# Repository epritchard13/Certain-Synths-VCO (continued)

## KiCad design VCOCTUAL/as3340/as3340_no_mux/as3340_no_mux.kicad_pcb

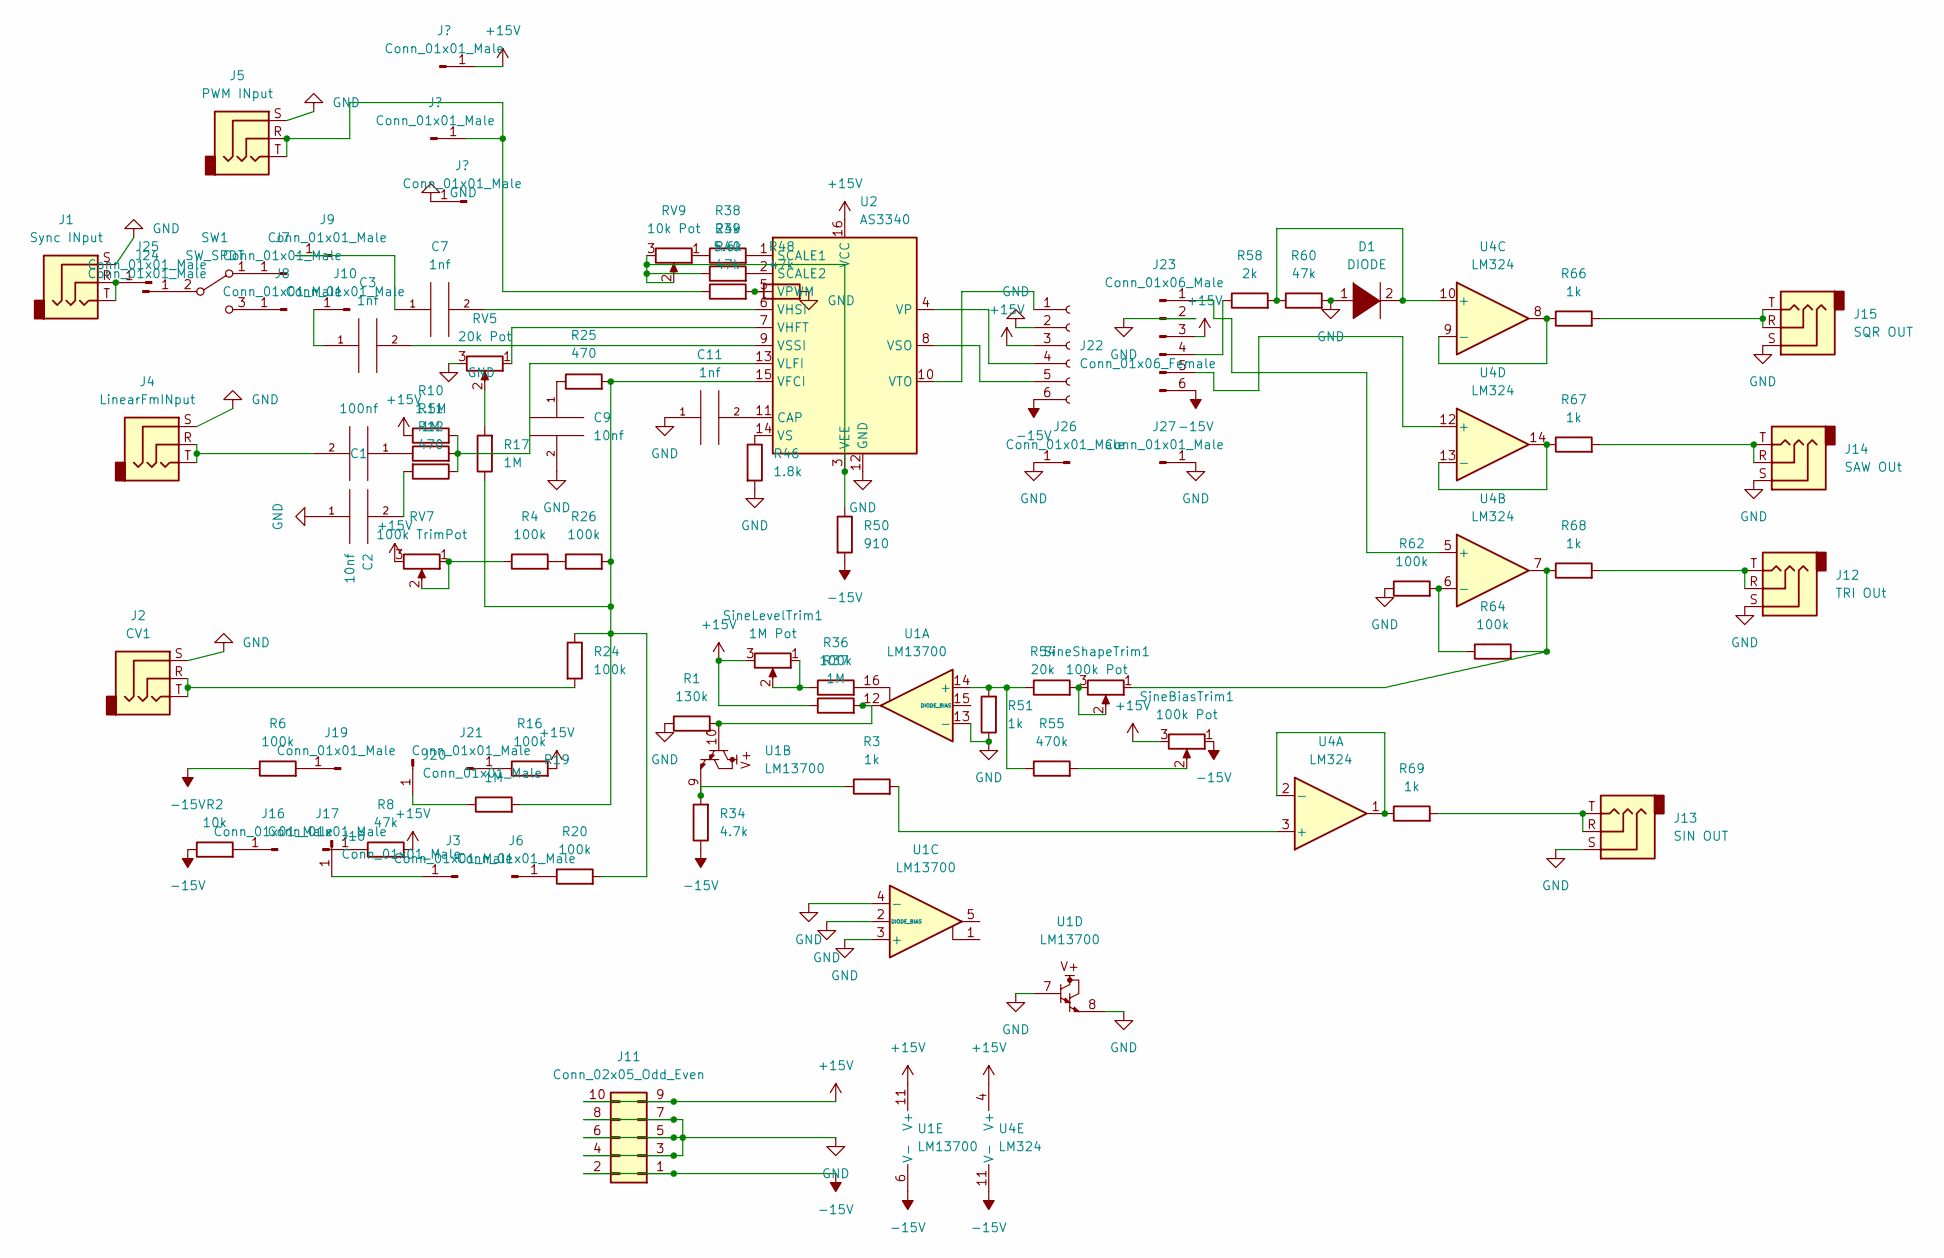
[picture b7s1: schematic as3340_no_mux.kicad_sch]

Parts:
C1: 100nf; C_Disc_D3.0mm_W1.6mm_P2.50mm
C2, C9: 10nf; C_1206_3216Metric_Pad1.33x1.80mm_HandSolder
C3, C7, C11: 1nf; C_1206_3216Metric_Pad1.33x1.80mm_HandSolder
D1: DIODE; C_Disc_D3.0mm_W1.6mm_P2.50mm
J1: Sync INput; Jack_3.5mm_Switronic_ST-005-G_horizontal
J2: CV1; Jack_3.5mm_Switronic_ST-005-G_horizontal
J3, J6, J7, J8, J9, J10, J16, J17, J18, J19, J20, J21, J24, J25, J26, J27: Conn_01x01_Male; PinHeader_1x01_P2.54mm_Vertical
J4: LinearFmINput; Jack_3.5mm_Switronic_ST-005-G_horizontal
J5: PWM INput; Jack_3.5mm_Switronic_ST-005-G_horizontal
J11: Conn_02x05_Odd_Even; PinHeader_2x05_P2.54mm_Vertical
J12: TRI OUt; Jack_3.5mm_Switronic_ST-005-G_horizontal
J13: SIN OUT; Jack_3.5mm_Switronic_ST-005-G_horizontal
J14: SAW OUt; Jack_3.5mm_Switronic_ST-005-G_horizontal
J15: SQR OUT; Jack_3.5mm_Switronic_ST-005-G_horizontal
J22: Conn_01x06_Female; PinHeader_1x06_P2.54mm_Vertical
J23: Conn_01x06_Male; PinHeader_1x06_P2.54mm_Vertical
R1: 130k; R_1206_3216Metric_Pad1.30x1.75mm_HandSolder
R2: 10k; R_1206_3216Metric_Pad1.30x1.75mm_HandSolder
R3, R51, R66, R67, R68, R69: 1k; R_1206_3216Metric_Pad1.30x1.75mm_HandSolder
R4, R6, R16, R20, R24, R26, R36, R62, R64: 100k; R_1206_3216Metric_Pad1.30x1.75mm_HandSolder
R8, R40, R48, R60: 47k; R_Axial_DIN0204_L3.6mm_D1.6mm_P5.08mm_Horizontal
R10: 1.5M; R_Axial_DIN0204_L3.6mm_D1.6mm_P5.08mm_Horizontal
R11, R17, R19, R37: 1M; R_Axial_DIN0204_L3.6mm_D1.6mm_P5.08mm_Horizontal
R12, R25: 470; R_1206_3216Metric_Pad1.30x1.75mm_HandSolder
R34: 4.7k; R_1206_3216Metric_Pad1.30x1.75mm_HandSolder
R38: 24k; R_1206_3216Metric_Pad1.30x1.75mm_HandSolder
R39: 5.6k; R_Axial_DIN0204_L3.6mm_D1.6mm_P5.08mm_Horizontal
R46: 1.8k; R_1206_3216Metric_Pad1.30x1.75mm_HandSolder
R50: 910; R_1206_3216Metric_Pad1.30x1.75mm_HandSolder
R54: 20k; R_1206_3216Metric_Pad1.30x1.75mm_HandSolder
R55: 470k; R_1206_3216Metric_Pad1.30x1.75mm_HandSolder
R58: 2k; R_1206_3216Metric_Pad1.30x1.75mm_HandSolder
RV5: 20k Pot; Potentiometer_ACP_CA6-H2,5_Horizontal
RV7: 100k TrimPot; Potentiometer_ACP_CA6-H2,5_Horizontal
RV9: 10k Pot; Potentiometer_ACP_CA6-H2,5_Horizontal
SW1: SW_SPDT; Potentiometer_ACP_CA6-H2,5_Horizontal
SineBiasTrim1: 100k Pot; Potentiometer_ACP_CA6-H2,5_Horizontal
SineLevelTrim1: 1M Pot; Potentiometer_ACP_CA6-H2,5_Horizontal
SineShapeTrim1: 100k Pot; Potentiometer_ACP_CA6-H2,5_Horizontal
U1: LM13700; DIP-16_W7.62mm
U2: AS3340; DIP-16_W7.62mm
U4: LM324; DIP-14_W7.62mm

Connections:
+15V: J11.9, J11.10, J22.3, J23.3, R8.2, R10.1, R16.2, R37.1, RV7.3, SineBiasTrim1.3, SineLevelTrim1.3, U1.11 (V+), U2.16 (VCC), U4.4 (V+)
-15V: J11.1, J11.2, J22.6, J23.6, R2.1, R6.1, R34.1, R50.2, SineBiasTrim1.1, U1.6 (V-), U4.11 (V-)
GND: C2.1, C9.2, C11.1, D1.1 (K), J1.S, J2.S, J4.S, J5.S, J11.3, J11.4, J11.5, J11.6, J11.7, J11.8, J12.S, J13.S, J14.S, J15.S, J22.2, J23.2, J26.1, J27.1, R1.1, R46.2, R48.2, R51.1, R60.2, R62.1, RV5.3, U1.2 (DIODE_BIAS), U1.3 (+), U1.4 (-), U1.7, U1.8, U1.13 (-), U2.12 (GND)
unnamed: C1.1, R11.1
unnamed: C1.2, J4.R, J4.T
unnamed: C2.2, R12.2
unnamed: C3.1, J10.1
unnamed: C3.2, U2.9 (VSSI)
unnamed: C7.1, J9.1
unnamed: C7.2, U2.6 (VHSI)
unnamed: C9.1, R25.1
unnamed: C11.2, U2.11 (CAP)
unnamed: D1.2 (A), R58.2, R60.1, U4.10 (+)
unnamed: J1.R, J1.T, J25.1
unnamed: J3.1, J18.1
unnamed: J7.1, SW1.1 (A)
unnamed: J8.1, SW1.3 (C)
unnamed: J22.1, U2.10 (VTO)
unnamed: J22.4, U2.4 (VP)
unnamed: J22.5, U2.8 (VSO)
unnamed: J24.1, SW1.2 (B)
unnamed: J16.1, R2.2
unnamed: J19.1, R6.2
unnamed: J17.1, R8.1
unnamed: R10.2, R11.2, R12.1, U2.13 (VLFI)
unnamed: J21.1, R16.1
unnamed: R17.1, R19.2, R20.2, R24.1, R25.2, R26.2, U2.15 (VFCI)
unnamed: R17.2, RV5.2
unnamed: J20.1, R19.1
unnamed: J6.1, R20.1
unnamed: J2.R, J2.T, R24.2
unnamed: R4.2, R26.1
unnamed: R3.1, R34.2, U1.9
unnamed: R36.1, SineLevelTrim1.1, SineLevelTrim1.2
unnamed: R36.2, U1.16
unnamed: R38.1, RV9.1
unnamed: R38.2, U2.1 (SCALE1)
unnamed: R39.1, R50.1, RV9.2, RV9.3, U2.3 (VEE)
unnamed: R39.2, U2.2 (SCALE2)
unnamed: J5.R, J5.T, R40.1
unnamed: R40.2, R48.1, U2.5 (VPWM)
unnamed: R46.1, U2.14 (VS)
unnamed: R51.2, R54.1, R55.1, U1.14 (+)
unnamed: R54.2, SineShapeTrim1.2, SineShapeTrim1.3
unnamed: R55.2, SineBiasTrim1.2
unnamed: J23.4, R58.1
unnamed: R62.2, R64.1, U4.6 (-)
unnamed: R64.2, R68.1, SineShapeTrim1.1, U4.7
unnamed: R66.1, U4.8, U4.9 (-)
unnamed: J15.R, J15.T, R66.2
unnamed: R67.1, U4.13 (-), U4.14
unnamed: J14.R, J14.T, R67.2
unnamed: J12.R, J12.T, R68.2
unnamed: R69.1, U4.1, U4.2 (-)
unnamed: J13.R, J13.T, R69.2
unnamed: RV5.1, U2.7 (VHFT)
unnamed: R4.1, RV7.1, RV7.2
unnamed: R1.2, R37.2, U1.10, U1.12
unnamed: R3.2, U4.3 (+)
unnamed: J23.1, U4.5 (+)
unnamed: J23.5, U4.12 (+)

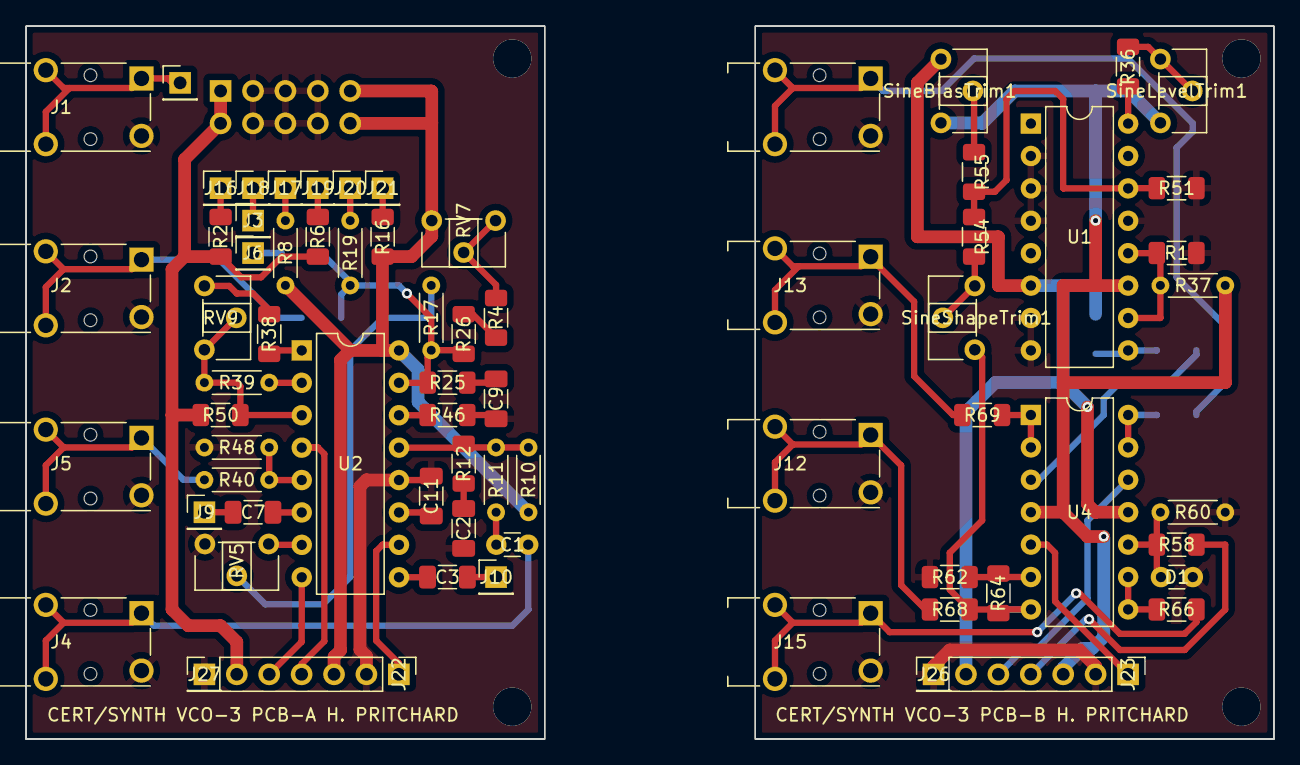
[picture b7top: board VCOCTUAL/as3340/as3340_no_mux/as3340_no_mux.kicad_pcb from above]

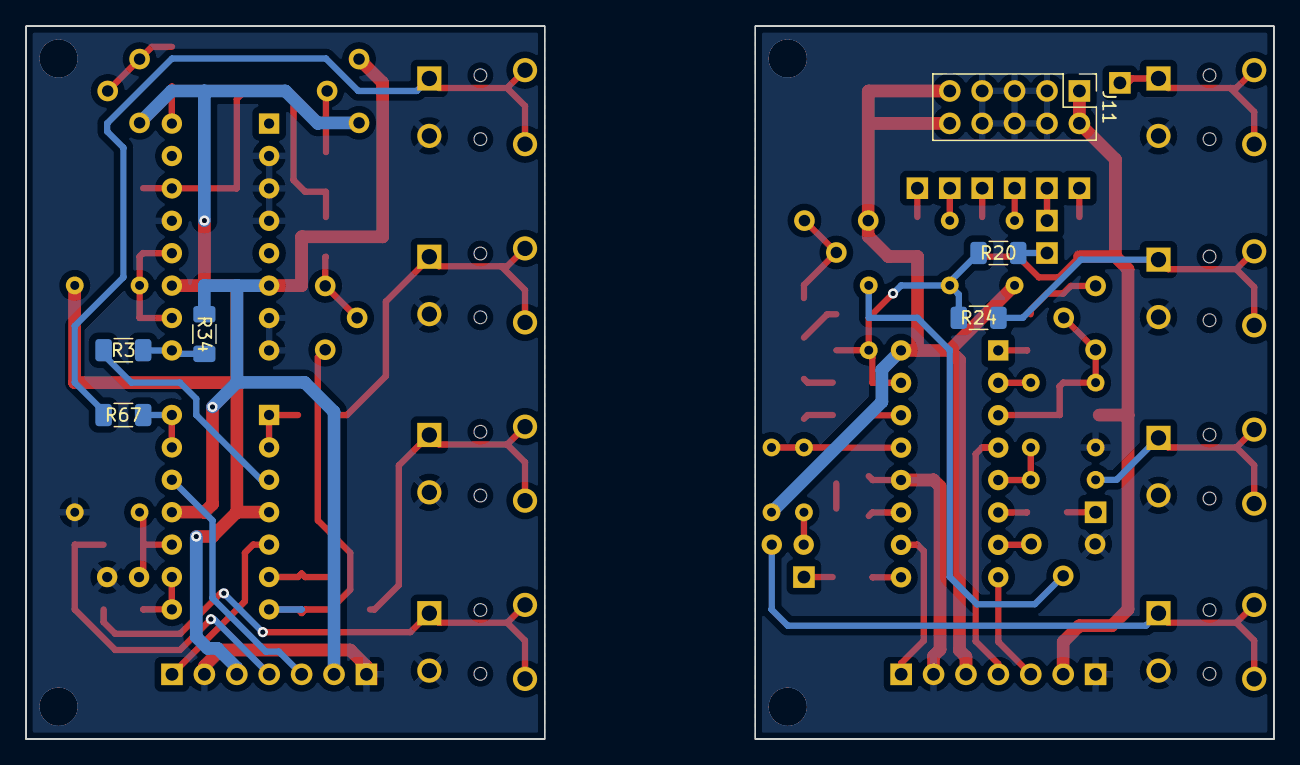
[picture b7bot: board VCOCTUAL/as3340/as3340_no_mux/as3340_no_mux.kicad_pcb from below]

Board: 2 copper layers, 97.8 x 55.9 mm, 76 parts (6 on the bottom side), 58 nets.

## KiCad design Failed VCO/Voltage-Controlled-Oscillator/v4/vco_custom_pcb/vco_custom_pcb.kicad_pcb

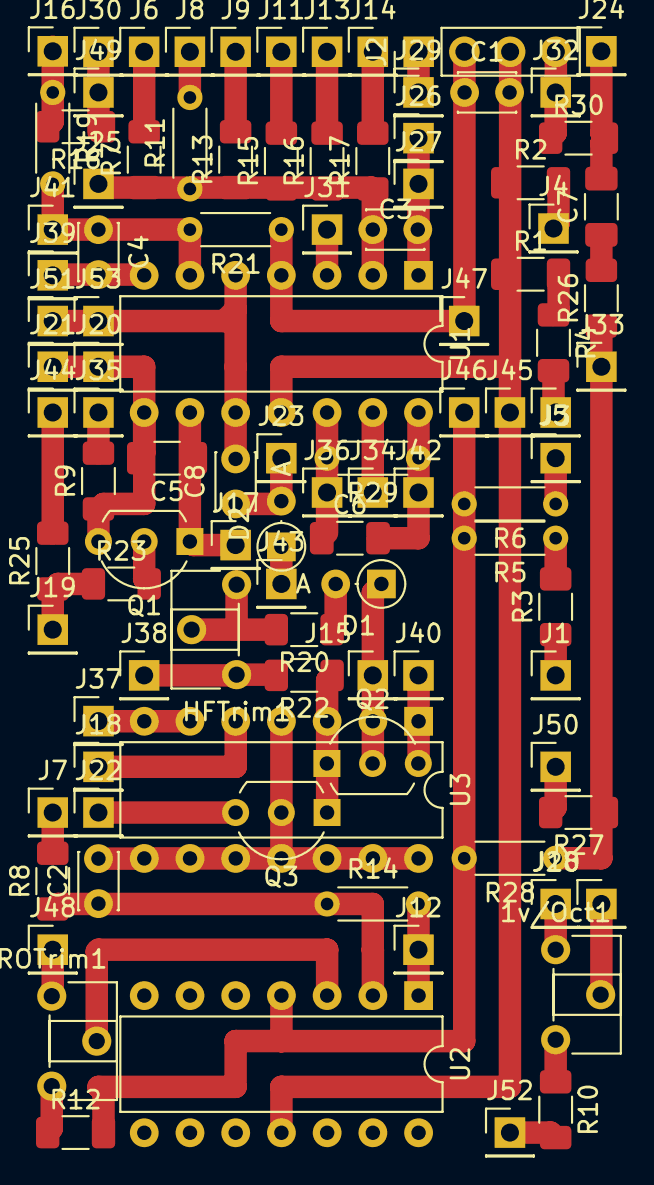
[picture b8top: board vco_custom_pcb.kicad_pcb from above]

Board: 2 copper layers, 101 parts (0 on the bottom side), 54 nets.

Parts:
1v/Oct1: 100; Potentiometer_ACP_CA6-H2,5_Horizontal
C1: .1uF; C_Disc_D3.0mm_W2.0mm_P2.50mm
C2: 0.1uF; C_Disc_D3.0mm_W2.0mm_P2.50mm
C3, C4, C8: 100pF; C_Disc_D3.0mm_W2.0mm_P2.50mm
C5: 0.005uF; C_1206_3216Metric_Pad1.33x1.80mm_HandSolder
C6: 4.7pF; C_1206_3216Metric_Pad1.33x1.80mm_HandSolder
C7: 0.001uF; C_1206_3216Metric_Pad1.33x1.80mm_HandSolder
D1, D2: DIODE; D_DO-35_SOD27_P2.54mm_Vertical_AnodeUp
HFTrim1: 100k; Potentiometer_ACP_CA6-H2,5_Horizontal
J1: TP1+; PinHeader_1x01_P2.54mm_Vertical
J2: Power; PinHeader_1x04_P2.54mm_Vertical
J3: TP2+; PinHeader_1x01_P2.54mm_Vertical
J4: TP2-; PinHeader_1x01_P2.54mm_Vertical
J5: TP1-; PinHeader_1x01_P2.54mm_Vertical
J6: TP1val; PinHeader_1x01_P2.54mm_Vertical
J7: RAWIN; PinHeader_1x01_P2.54mm_Vertical
J8: TP2val; PinHeader_1x01_P2.54mm_Vertical
J9: CVIN 1; PinHeader_1x01_P2.54mm_Vertical
J10: LINOUT; PinHeader_1x01_P2.54mm_Vertical
J11: CVIN 2; PinHeader_1x01_P2.54mm_Vertical
J12: RAMPOUT; PinHeader_1x01_P2.54mm_Vertical
J13: CVIN 3; PinHeader_1x01_P2.54mm_Vertical
J14: CVIN 4; PinHeader_1x01_P2.54mm_Vertical
J15: LININ; PinHeader_1x01_P2.54mm_Vertical
J16: LIN Adj; PinHeader_1x01_P2.54mm_Vertical
J17: EXPIN; PinHeader_1x01_P2.54mm_Vertical
J18, J22: EXPOUT; PinHeader_1x01_P2.54mm_Vertical
J19, J23: JUMPER00; PinHeader_1x01_P2.54mm_Vertical
J20: RAW; PinHeader_1x01_P2.54mm_Vertical
J21: RAWOUT; PinHeader_1x01_P2.54mm_Vertical
J24: SYNC; PinHeader_1x01_P2.54mm_Vertical
J25: tempco m1; PinHeader_1x01_P2.54mm_Vertical
J26: tempco m2; PinHeader_1x01_P2.54mm_Vertical
J27: sumamp1; PinHeader_1x01_P2.54mm_Vertical
J28: sumamp2; PinHeader_1x01_P2.54mm_Vertical
J29: gndj0; PinHeader_1x01_P2.54mm_Vertical
J30: gndj3; PinHeader_1x01_P2.54mm_Vertical
J31: gndj1; PinHeader_1x01_P2.54mm_Vertical
J32: gndj2; PinHeader_1x01_P2.54mm_Vertical
J33: JUMPER2; PinHeader_1x01_P2.54mm_Vertical
J34: JUMPER3; PinHeader_1x01_P2.54mm_Vertical
J35: JUMPER5; PinHeader_1x01_P2.54mm_Vertical
J36: JUMPER4; PinHeader_1x01_P2.54mm_Vertical
J37, J48, J49, J50, J51, J52, J53: gnd; PinHeader_1x01_P2.54mm_Vertical
J38: jumper10; PinHeader_1x01_P2.54mm_Vertical
J39: jumper11; PinHeader_1x01_P2.54mm_Vertical
J40: jumper13; PinHeader_1x01_P2.54mm_Vertical
J41: jumper12; PinHeader_1x01_P2.54mm_Vertical
J42: JUMPER14; PinHeader_1x01_P2.54mm_Vertical
J43: JUMPER15; PinHeader_1x01_P2.54mm_Vertical
J44, J45: minus12; PinHeader_1x01_P2.54mm_Vertical
J46, J47: plus12; PinHeader_1x01_P2.54mm_Vertical
Q1, Q2, Q3: 2N3904; TO-92L_Inline_Wide
R1, R3, R4, R7, R12, R13, R15, R16, R17, R18, R23, R30: 100k; R_1206_3216Metric_Pad1.30x1.75mm_HandSolder
R2, R8, R9, R22: 10k; R_1206_3216Metric_Pad1.30x1.75mm_HandSolder
R5: 100k; R_Axial_DIN0204_L3.6mm_D1.6mm_P5.08mm_Horizontal
R6, R14: 47k; R_Axial_DIN0204_L3.6mm_D1.6mm_P5.08mm_Horizontal
R10: 475; R_1206_3216Metric_Pad1.30x1.75mm_HandSolder
R11, R19, R21, R29: 1M; R_Axial_DIN0204_L3.6mm_D1.6mm_P5.08mm_Horizontal
R20: 4.7k; R_1206_3216Metric_Pad1.30x1.75mm_HandSolder
R25: 18k; R_1206_3216Metric_Pad1.30x1.75mm_HandSolder
R26: 1k; R_1206_3216Metric_Pad1.30x1.75mm_HandSolder
R27: 2k; R_1206_3216Metric_Pad1.30x1.75mm_HandSolder
R28: 10k; R_Axial_DIN0204_L3.6mm_D1.6mm_P5.08mm_Horizontal
ROTrim1: 10k; Potentiometer_ACP_CA6-H2,5_Horizontal
U1, U2, U3: LM324; DIP-14_W7.62mm

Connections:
+12V: C1.1, J2.2, J46.1, J47.1, R5.2, R6.2, R12.2, R21.1, R28.2, U1.4 (V+), U2.4 (V+)
-12V: C1.2, J2.3, J45.1, R1.1, R2.1, U1.11 (V-), U2.11 (V-)
GND: C2.2, C8.2, J2.1, J2.4, J29.1, J30.1, J31.1, J32.1, J49.1, J51.1, J53.1, Q3.2 (B), R18.1, R30.1, U1.3 (+), U1.5 (+), U1.10 (+), U3.4 (V+), U3.8, U3.9 (-), U3.10 (+), U3.11 (V-), U3.12 (+), U3.13 (-), U3.14
unnamed: 1v/Oct1.1, J28.1
unnamed: 1v/Oct1.2, J10.1
unnamed: 1v/Oct1.3, R10.1
unnamed: C2.1, R8.1, R14.1, U2.2 (-)
unnamed: C3.1, J25.1, R7.1, R11.1, R13.1, R15.1, R16.1, R17.1, U1.2 (-)
unnamed: C3.2, J26.1, J27.1, U1.1
unnamed: C4.1, J41.1, R19.2, R21.2, U1.6 (-)
unnamed: C4.2, J39.1, U1.7
unnamed: C5.1, J17.1, Q1.1 (E), U1.9 (-)
unnamed: C5.2, J20.1, J21.1, Q1.3 (C), R9.1, U1.8
unnamed: C6.1, J36.1, R29.2, U1.12 (+)
unnamed: C6.2, J42.1, R29.1, U1.14
unnamed: C7.1, R26.2
unnamed: C7.2, J24.1, R30.2
unnamed: C8.1, D2.2 (A), J23.1
unnamed: D1.1 (K), J15.1, Q2.2 (B), U3.2 (-)
unnamed: D1.2 (A), R20.1
unnamed: D2.1 (K), J43.1
unnamed: HFTrim1.1, J38.1, R22.2
unnamed: HFTrim1.2, HFTrim1.3, R20.2
unnamed: J1.1, R3.1
unnamed: J3.1, R6.1
unnamed: J4.1, R2.2
unnamed: J5.1, R4.2
unnamed: J6.1, R7.2
unnamed: J7.1, R8.2
unnamed: J8.1, R11.2
unnamed: J9.1, R13.2
unnamed: J11.1, R15.2
unnamed: J12.1, R14.2, U2.1
unnamed: J13.1, R16.2
unnamed: J14.1, R17.2
unnamed: J16.1, R18.2, R19.1
unnamed: J18.1, U3.5 (+)
unnamed: J19.1, R23.1, R25.1
unnamed: J22.1, Q3.3 (C)
unnamed: J33.1, R26.1, R27.1, R28.1
unnamed: J34.1, U1.13 (-)
unnamed: J35.1, R9.2
unnamed: J37.1, U3.6 (-), U3.7
unnamed: J40.1, Q2.3 (C), U3.1
unnamed: J44.1, R25.2
unnamed: Q1.2 (B), R23.2
unnamed: Q2.1 (E), Q3.1 (E), R22.1, U3.3 (+)
unnamed: R1.2, R4.1
unnamed: R3.2, R5.1
unnamed: J52.1, R10.2
unnamed: R12.1, ROTrim1.3
unnamed: J50.1, R27.2
unnamed: J48.1, ROTrim1.1
unnamed: ROTrim1.2, U2.3 (+)

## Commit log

2023-03-25 Uploading existing work
2023-06-08 Test
    Test
2023-06-08 VCA Folder
2023-06-08 vca schematic
    test
2023-06-08 adding da cool vco
    da ral 1
2023-06-08 Power Supply
    POWER
2023-06-08 Picture
2023-06-08 Update README.md
    lesgo!
2023-06-08 Create Why the VCO is resonating
2023-06-08 LFO
    Added LFO
2023-06-08 updated yo kengiz yawn guh bubby pirket
    bubdaped yo dingdabing pep ring rong geeee renni
2023-06-09 power
2023-06-09 minor power supply changes
2023-06-12 Huge VCO Update
2023-06-12 made schematic goof
    not it good
2023-06-12 Very Epic 2 layer VCO
2023-06-12 How????
2023-06-12 fp
    front panel
2023-06-13 Redone VCO Layout
    Added the switch and made trace width .2mm
2023-06-14 pics
2023-06-20 l
    l
2023-06-26 HUGE VCO UPDATE FOR AUTOMATION
2023-07-13 wowzas
2023-07-13 hhgreg
2023-07-15 zipz
    zips
2023-07-22 midi to cv controller
2023-10-11 thonkycon king poo nigo chanel type vca
2023-10-23 pittyboi piss
